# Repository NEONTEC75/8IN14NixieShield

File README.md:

# 8IN14NixieShield
This shield is just a minimal Nixie multiplexed circuit and contains the following components:
- 74141 nixie cathode driver IC (pins 4, 6, 7, 5);
- TLP627 opto-couplers for anodes (pins 12, 11, 9, 8, 10, A1, A2, A3);
- 3-button resistive keyboard (A3);
- simple boost converter driven by Arduino's PWM (pin 3, and pin A0 for output voltage feedback);
- DS3231 module connector;
- A 9/RHDP jumper on tube #2. You can build a Divergence Meter based on this shield.

The library with some examples:
https://github.com/NEONTEC75/NixieLib

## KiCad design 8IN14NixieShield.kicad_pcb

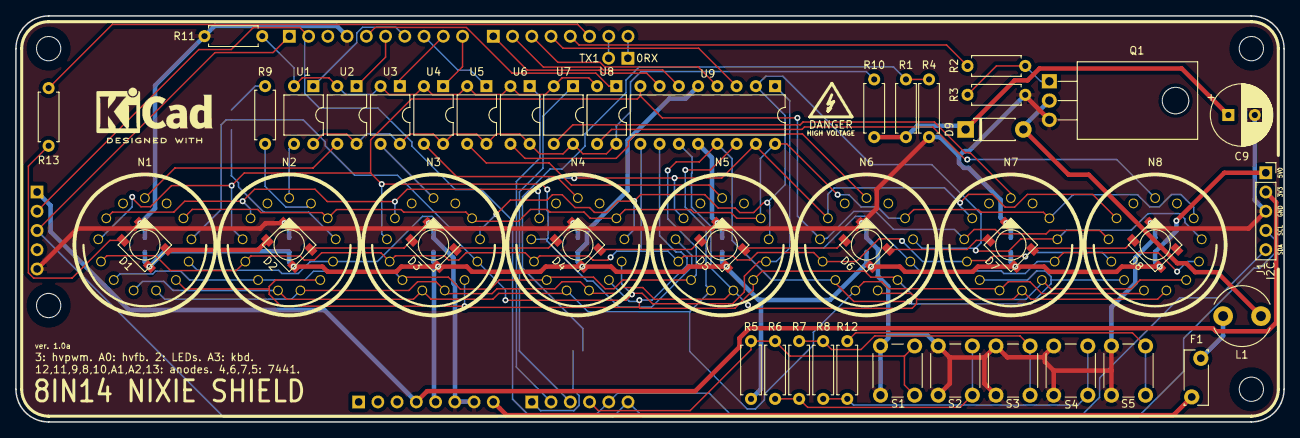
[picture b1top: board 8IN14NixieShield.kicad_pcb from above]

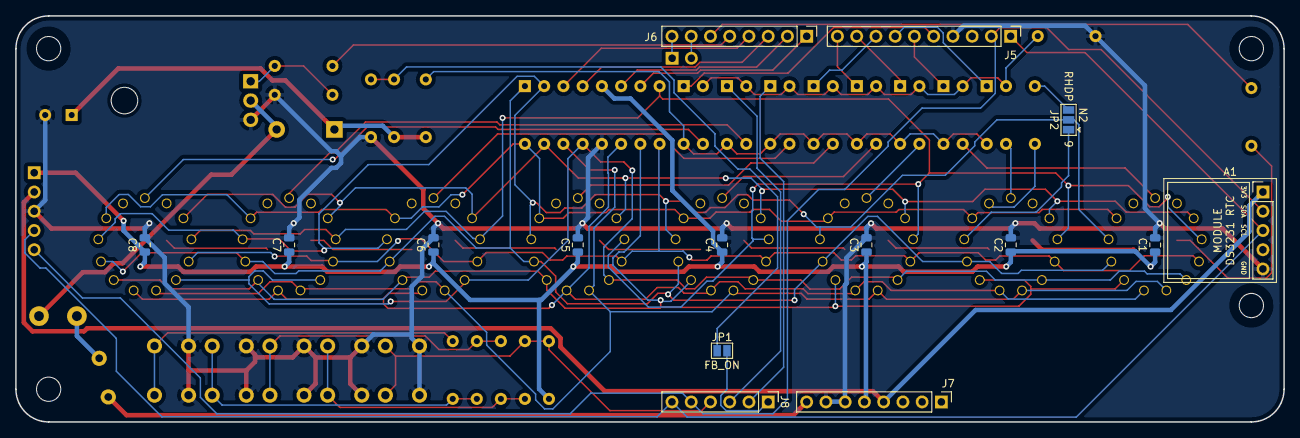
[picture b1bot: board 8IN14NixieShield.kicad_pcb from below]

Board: 2 copper layers, 167.4 x 53.6 mm, 70 parts (15 on the bottom side), 64 nets.

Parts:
A1: DS3231
C1, C2, C3, C4, C5, C6, C7, C8: 100n; C_0805_2012Metric
C9: 4.7uF*350V; CP_Radial_D8.0mm_P3.50mm
D1, D2, D3, D4, D5, D6, D7, D8: WS2812B
D9: HER106; D_DO-41_SOD81_P7.62mm_Horizontal
F1: 1A; Fuse_Bourns_MF-RG300
H1, H2, H3, H4: MountingHole; MountingHole_3.2mm_M3_DIN965
J1: I2C; PinSocket_1x05_P2.54mm_Vertical
J4: EXT2; PinHeader_1x02_P2.54mm_Vertical
J5: UNO3; PinHeader_1x10_P2.54mm_Vertical
J6: UNO4; PinHeader_1x08_P2.54mm_Vertical
J7: UNO1; PinHeader_1x08_P2.54mm_Vertical
J8: UNO2; PinHeader_1x06_P2.54mm_Vertical
JP1: FB_ON; SolderJumper-2_P1.3mm_Open_Pad1.0x1.5mm
JP2: 9/RHDP; SolderJumper-3_P1.3mm_Open_Pad1.0x1.5mm
KICADLOGO: KiCad-Logo2_6mm_SilkScreen
L1: 470uH; L_Radial_D7.8mm_P5.00mm_Fastron_07HCP
N1, N2, N3, N4, N5, N6, N7, N8: IN-14; IN-14new
Q1: IRF740; TO-220-3_Horizontal_TabDown
R1: 300k; R_Axial_DIN0207_L6.3mm_D2.5mm_P7.62mm_Horizontal
R2: 22; R_Axial_DIN0207_L6.3mm_D2.5mm_P7.62mm_Horizontal
R3: 100k; R_Axial_DIN0207_L6.3mm_D2.5mm_P7.62mm_Horizontal
R4, R9: 4k7; R_Axial_DIN0207_L6.3mm_D2.5mm_P7.62mm_Horizontal
R5, R6, R7, R8, R12: 10k; R_Axial_DIN0207_L6.3mm_D2.5mm_P7.62mm_Horizontal
R10: 2k2; R_Axial_DIN0207_L6.3mm_D2.5mm_P7.62mm_Horizontal
R11: 470; R_Axial_DIN0207_L6.3mm_D2.5mm_P7.62mm_Horizontal
R13: 100; R_Axial_DIN0207_L6.3mm_D2.5mm_P7.62mm_Horizontal
S1, S2, S3, S4, S5: SW_Push; SW_PUSH_6mm_H4.3mm
U1, U2, U3, U4, U5, U6, U7, U8: TLP627; DIP-4_W7.62mm
U9: K155ID1; DIP-16_W7.62mm

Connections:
+3V3: A1.1, J1.2, J7.4
+5V: C1.1, C2.1, C3.1, C4.1, C5.1, C6.1, C7.1, C8.1, D1.1, D2.1, D3.1, D4.1, D5.1, D6.1, D7.1, D8.1, J1.1, J7.5, R5.1, U9.5
/+HV: C9.1, D9.1, R1.2, R10.1
/A0: J8.1, JP1.2
/A1: J8.2, U6.1
/A2: J8.3, U7.1
/A3: J8.4, R5.2, R6.1, S1.1
/A4: A1.2, J1.5, J5.2, J8.5
/A5: A1.3, J1.4, J5.1, J8.6
/ACTL_1: J5.6, U2.1
/ACTL_2: J5.7, U1.1
/ACTL_3: J5.9, U3.1
/ACTL_4: J5.10, U4.1
/ACTL_5: J5.8, U5.1
/ACTL_8: J5.5, U8.1
/BOOST_PWM: J6.5, R2.2
/D0: J4.1, J6.8
/D1: J4.2, J6.7
/D2: J6.6, R13.1
/D4: J6.4, U9.3
/D5: J6.3, U9.4
/D6: J6.2, U9.6
/D7: J6.1, U9.7
/NixieCtl/ANODE_1: N1.A, U2.3
/NixieCtl/ANODE_2: N2.A, U1.3
/NixieCtl/ANODE_3: N3.A, U3.3
/NixieCtl/ANODE_4: N4.A, U4.3
/NixieCtl/ANODE_5: N5.A, U5.3
/NixieCtl/ANODE_6: N6.A, U6.3
/NixieCtl/ANODE_7: N7.A, U7.3
/NixieCtl/ANODE_8: N8.A, U8.3
/NixieCtl/CATHODE_0: N1.0, N2.0, N3.0, N4.0, N5.0, N6.0, N7.0, N8.0, U9.16
/NixieCtl/CATHODE_1: N1.1, N2.1, N3.1, N4.1, N5.1, N6.1, N7.1, N8.1, U9.15
/NixieCtl/CATHODE_2: N1.2, N2.2, N3.2, N4.2, N5.2, N6.2, N7.2, N8.2, U9.8
/NixieCtl/CATHODE_3: N1.3, N2.3, N3.3, N4.3, N5.3, N6.3, N7.3, N8.3, U9.9
/NixieCtl/CATHODE_4: N1.4, N2.4, N3.4, N4.4, N5.4, N6.4, N7.4, N8.4, U9.13
/NixieCtl/CATHODE_5: N1.5, N2.5, N3.5, N4.5, N5.5, N6.5, N7.5, N8.5, U9.14
/NixieCtl/CATHODE_6: N1.6, N2.6, N3.6, N4.6, N5.6, N6.6, N7.6, N8.6, U9.11
/NixieCtl/CATHODE_7: N1.7, N2.7, N3.7, N4.7, N5.7, N6.7, N7.7, N8.7, U9.10
/NixieCtl/CATHODE_8: N1.8, N2.8, N3.8, N4.8, N5.8, N6.8, N7.8, N8.8, U9.1
/NixieCtl/CATHODE_9: JP2.2, N1.9, N3.9, N4.9, N5.9, N6.9, N7.9, N8.9, U9.2
/VIN: F1.1, J7.8
GND: A1.5, C1.2, C2.2, C3.2, C4.2, C5.2, C6.2, C7.2, C8.2, C9.2, D1.3, D2.3, D3.3, D4.3, D5.3, D6.3, D7.3, D8.3, J1.3, J5.4, J7.6, J7.7, Q1.3, R3.2, R4.1, R11.2, S1.2, S2.2, S3.2, S4.2, S5.2, U9.12
unnamed: D1.2, D2.4
unnamed: D1.4, R13.2
unnamed: D2.2, D3.4
unnamed: D3.2, D4.4
unnamed: D4.2, D5.4
unnamed: D5.2, D6.4
unnamed: D6.2, D7.4
unnamed: D7.2, D8.4
unnamed: D9.2, L1.1, Q1.2
unnamed: F1.2, L1.2
unnamed: JP1.1, R1.1, R4.2
unnamed: JP2.1, N2.9
unnamed: JP2.3, R9.1
unnamed: N2.RHDP, R9.2
unnamed: Q1.1, R2.1, R3.1
unnamed: R6.2, R7.1, S2.1
unnamed: R7.2, R8.1, S3.1
unnamed: R10.2, U1.4, U2.4, U3.4, U4.4, U5.4, U6.4, U7.4, U8.4
unnamed: R11.1, U1.2, U2.2, U3.2, U4.2, U5.2, U6.2, U7.2, U8.2
unnamed: R8.2, R12.1, S4.1
unnamed: R12.2, S5.1
